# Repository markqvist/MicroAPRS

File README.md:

MicroAPRS
==========

__Important!__ _For new projects, please consider using [OpenModem](https://github.com/markqvist/OpenModem) as a platform instead. It is much more powerful, and has none of the limitations of this implementation. For simple projects, MicroAPRS is absolutely still usable, and it is incredibly stable and well-tested in thousands of hours of real-life usage, but have a look at OpenModem as well, since that is what I will be maintaining from now on. No new features or updates will be added to MicroAPRS from here on. I consider it stable and feature-complete for what the hardware is capable of._

MicroAPRS is an APRS firmware for [MicroModem](http://unsigned.io/micromodem). It supports both normal KISS mode, and a simple serial protocol for easy communication with an Arduino, or other MCU.

You can buy a complete modem from [my shop](http://unsigned.io/shop), or you can build one yourself pretty easily. Take a look at the documentation in the [MicroModem](https://github.com/markqvist/MicroModem) repository for information and getting started guides!

## Some features

- Send and receive AX.25 APRS packets
- Full modulation and demodulation in software
- Easy configuration of callsign and path settings
- Flexibility in how received packets are output over serial connection
- Persistent configuration stored in EEPROM
- Shorthand functions for sending location updates and messages, so you don't need to manually create the packets
- Ability to send raw packets
- Support for settings APRS symbols
- Support for power/height/gain info in location updates
- Ability to automatically ACK messages adressed to the modem
- Can run with open squelch
- Supports KISS mode for use with programs on a host computer

## KISS mode

When the modem is running in KISS mode, there's really not much more to it than connecting the modem to a computer, opening whatever program you want to use with it, and off you go.

When in KISS mode, the preamble time, tail time, persistence and slot time parameters can be configured by the default KISS commands for these. See KISS.h and KISS.c for more info on the configuration command syntax. 

It's important to note that some programs (Xastir, for example) will reset the modem when connecting to it, and then immediately send configuration commands. Depending on your hardware, this might have the unfortunate effect that the configuration commands are sent to the bootloader, instead of the booted firmware. If your program does not allow you to disable resetting or to set a delay for sending the configuration commands, you can manually disable the reset functionality by connecting a resistor of around 100 ohms between the VCC and DTR pins. This will ensure that the modem is not reset, even if the host program sends a reset command.

## Modem control - SimpleSerial

If you want to use the SimpleSerial protocol, here's how to control the APRS modem over a serial connection. The modem accepts a variety of commands for setting options and sending packets. Generally a command starts with one or more characters defining the command, and then whatever data is needed to set the options for that command. Here's a list of the currently available commands:

## Serial commands

Command | Description
--- | :---
__!\<data>__  | Send raw packet
__@\<cmt>__ | Send location update (cmt = optional comment)
__#\<msg>__ | Send APRS message
&nbsp; | &nbsp;
__c\<call>__ |  Set your callsign
__d\<call>__ |  Set destination callsign
__1\<call>__ |  Set PATH1 callsign
__2\<call>__ |  Set PATH2 callsign
&nbsp; | &nbsp;
__sc\<ssid>__ | Set your SSID
__sd\<ssid>__ | Set destination SSID
__s1\<ssid>__ | Set PATH1 SSID
__s2\<ssid>__ | Set PATH2 SSID
&nbsp; | &nbsp;
__lla\<LAT>__ | Set latitude (NMEA-format, eg 4903.50N)
__llo\<LON>__ | Set latitude (NMEA-format, eg 07201.75W)
__lp\<0-9>__  | Set TX power info
__lh\<0-9>__  | Set antenna height info
__lg\<0-9>__  | Set antenna gain info
__ld\<0-9>__  | Set antenna directivity info
__ls\<sym>__  | Select symbol
__lt\<s/a>__  | Select symbol table (standard/alternate)
&nbsp; | &nbsp;
__mc\<call>__ | Set message recipient callsign
__ms\<ssid>__ | Set message recipient SSID
__mr\<ssid>__ | Retry last message
__ma\<1/0>__  | Automatic message ACK on/off
&nbsp; |&nbsp;
__ps\<1/0>__  | Print SRC on/off
__pd\<1/0>__  | Print DST on/off
__pp\<1/0>__  | Print PATH on/off
__pm\<1/0>__  | Print DATA on/off
__pi\<1/0>__  | Print INFO on/off
__v\<1/0>__ | Verbose mode on/off
__V\<1/0>__ | Silent mode on/off
&nbsp; | &nbsp;
__w\<XXX>__ | Set preamble in ms
__W\<XXX>__ | Set TX tail in ms
&nbsp; | &nbsp;
__S__ | Save configuration
__L__ | Load configuration
__C__ | Clear configuration
__H__ | Print configuration

### Examples

__To set your callsign to XX1YYY-5, and then save the configuration, send these three commands:__
```
cXX1YYY
sc5
S
```

__To send an APRS message to ZZ5ABC-1 with the content "Hi there!", send these commands:__
```
mcZZ5ABC
ms1
# Hi there!
```

__To send a location update, with the comment "MicroAPRS", you can do something like this:__
```
lla5230.70N
llo01043.70E
@MicroAPRS
```

__To send an APRS message to ZZ5ABC-1 with the content "Hi there!", using a raw packet, send this command:__
```
!:ZZ5ABC-1 :Hi there!{01
```
__Here's an example of how to send a location update with power, height and gain information, using a raw packet:__
```
!=5230.70N/01043.70E-PHG2410MicroAPRS
```

### EEPROM Settings
When saving the configuration, it is written to EEPROM, so it will persist between poweroffs. If a configuration has been stored, it will automatically be loaded when the modem powers up. The configuration can be cleared by sending the "clear configuration" command (`C`).

### Serial Connection

To connect to the modem use __9600 baud, 8N1__ serial. By default, the firmware uses time-sensitive input, which means that it will buffer serial data as it comes in, and when it has received no data for a few milliseconds, it will start interpreting whatever it has received. This means you need to set your serial terminal program to not send data for every keystroke, but only on new-line, or pressing send or whatever. If you do not want this behaviour, you can compile the firmware with the DEBUG flag set, which will make the modem wait for a new-line character before interpreting the received data. I would generally advise against this though, since it means that you cannot have newline characters in whatever data you want to send!

The project has been implemented in your normal C with makefile style, and uses AVR Libc. The firmware is compatible with Arduino-based products, although it was not written in the Arduino IDE.

Visit [my site](http://unsigned.io) for questions, comments and other details.

## Support Me
If you have benefited from this project, you can help support the continued development of open, free and private communications systems by donating via one of the following channels:

- Ethereum: 0x81F7B979fEa6134bA9FD5c701b3501A2e61E897a
- Bitcoin: 3CPmacGm34qYvR6XWLVEJmi2aNe3PZqUuq
- Ko-Fi: https://ko-fi.com/markqvist

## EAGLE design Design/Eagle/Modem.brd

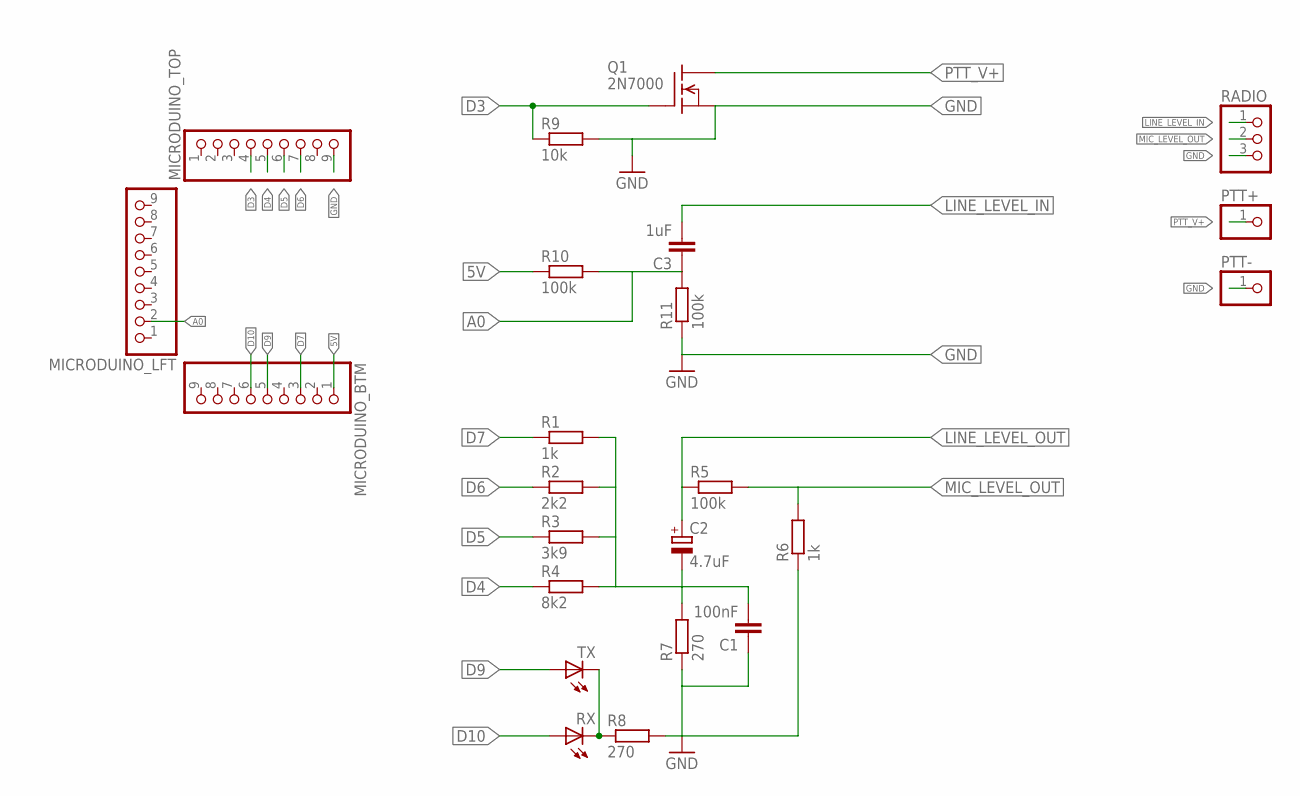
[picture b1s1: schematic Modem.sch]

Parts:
C1: 100nF; C2.5-2
C2: 4.7uF; E2,5-4R
C3: 1uF; C2.5-2
MICRODUINO_BTM: PINHD-1X9; 1X09-BIG
MICRODUINO_LFT: PINHD-1X9; 1X09-BIG
MICRODUINO_TOP: PINHD-1X9; 1X09-BIG
PTT+: PINHD-1X1; 1X01
PTT-: PINHD-1X1; 1X01
Q1: 2N7000; TO92
R1, R6: 1k; 0204V
R2: 2k2; 0204V
R3: 3k9; 0204V
R4: 8k2; 0204V
R5, R10, R11: 100k; 0204V
R7, R8: 270; 0204V
R9: 10k; 0204V
RADIO: PINHD-1X3; 1X03
RX: LED_ELD260; LED_LD260
TX: LED_ELD260; LED_LD260

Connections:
5V: MICRODUINO_BTM.1, R10.1
A0: C3.1, MICRODUINO_LFT.2, R10.2, R11.2
D3: MICRODUINO_TOP.4, Q1.1 (G), R9.1
D4: MICRODUINO_TOP.5, R4.1
D5: MICRODUINO_TOP.6, R3.1
D6: MICRODUINO_TOP.7, R2.1
D7: MICRODUINO_BTM.3, R1.1
D9: MICRODUINO_BTM.5, TX.A
D10: MICRODUINO_BTM.6, RX.A
GND: C1.1, MICRODUINO_TOP.9, PTT-.1, Q1.3 (S), R6.1, R7.1, R8.2, R9.2, R11.1, RADIO.3
LINE_LEVEL_IN: C3.2, RADIO.1
LINE_LEVEL_OUT: C2.+, R5.1
MIC_LEVEL_OUT: R5.2, R6.2, RADIO.2
unnamed: R8.1, RX.K (C), TX.K (C)
unnamed: C1.2, C2.-, R1.2, R2.2, R3.2, R4.2, R7.2
PTT_V+: PTT+.1, Q1.2 (D)

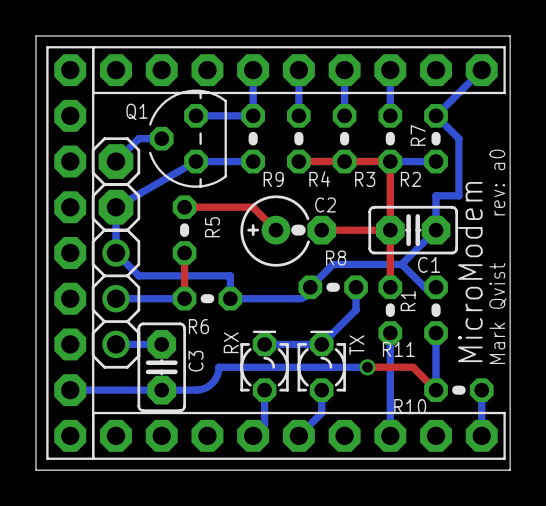
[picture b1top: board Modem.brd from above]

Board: 2 copper layers, 26.3 x 24.1 mm, 23 parts (0 on the bottom side), 16 nets.

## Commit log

2014-04-03 Working
2014-04-03 Buildrev
2014-04-03 Removed stuff
2014-04-03 Cleanup
2014-04-03 Still working
2014-04-03 Before afsk refactor
2014-04-03 Reworked AFSK Struct
2014-04-03 Reworked HDLC struct
2014-04-03 Reworked afsk init. Found the error :P
2014-04-03 Migrated adc_isr
2014-04-03 Migrated HDLC
2014-04-03 Migrated hardware
2014-04-03 Temporary AX.25 include for testing
2014-04-04 Reworked DAC ISR
2014-04-04 Reworked KFile read
2014-04-04 Reworked KFile write
2014-04-04 Reworked remaining KFile functions
2014-04-04 MP1 protocol receive implemented
2014-04-04 MP1 Transmit. Basic iplementation done.
2014-04-04 Implemented checksumming
2014-04-06 Commenting
2014-04-06 More commenting
2014-04-06 Cleaned up port mapping mess
2014-04-06 Removed dacPin sillyness
2014-04-06 Stuff not working
2014-04-07 Changed decode phase window
2014-04-07 Preamble timing
2014-04-07 Phase sync experiments
2014-04-08 Before PLL algo adjust
2014-04-09 Updated doc. Cleanup.
2014-04-10 Before AX.25 test
2014-04-10 After AX.25 decode test. 902 packets decoded.
2014-04-13 Before Hamming code
2014-04-13 Work on error correction
2014-04-13 Protocol-level (12,8) hamming code implemented
2014-04-13 Very short preamble
2014-04-14 After compression lib experiment
2014-04-14 Successfull compression test with heatshrink
2014-04-14 Compression tested over the air
2014-04-15 Before interleaver
2014-04-16 Interleaver implemented
2014-04-16 Updated documentation
2014-04-16 Fixed escape char bug
2014-04-17 12-byte interleaver
2014-04-17 12-byte interleaver, (12,8)-Hamming code and compression tested successfully
2014-04-23 8N1 Serial
2014-04-27 Direct serial line in/out. P-persistent CSMA. SLIP compatibility.
2014-04-27 Compression on/off compile option.
2014-04-28 Various TCP/IP experiments
2014-04-28 TCP mode
2014-04-29 Added schematics
2014-04-29 Update radme
2014-04-29 Updated Microduino PCB
2014-04-30 Update fritzing file
2014-04-30 Eagle files
2014-04-30 Added 3D sources for case
2014-04-30 Cast to signed int to squelch compiler warning
2014-04-30 Eagle PCB
2014-05-13 PCB confirmed
2014-05-13 Added photos
2014-05-13 Added photo
2014-05-16 Added binaries to repo
2014-05-17 Added license
2014-05-17 Added file
2014-05-17 Updated build instructions
2014-05-20 Added some documentation
2014-05-20 Updated quickstart
2014-05-20 Indentation mess cleanup
2014-05-29 32u4 experiment
2014-05-29 AX25 demo
2014-05-29 APRS demonstration
2014-06-18 Implemented simple serial control protocol for APRS stuff.
2014-06-18 Removed accidentially set frequency correction
2014-06-19 Implemented EEPROM settings
2014-06-19 Various simplifications and serial control improvements
2014-06-19 Implemented easy location update sending
2014-06-19 Implemented APRS messaging support
2014-06-19 Before auto-ack
2014-06-19 Implemented message auto-ack
2014-06-19 Update build
2014-06-23 Slimmed down binary
2014-06-23 Frame buf length define fixed
2014-06-24 Slimmed down BertOS AX25
2014-06-24 Fixed ack bug
2014-06-24 Fixed SSID config bug
2014-09-10 Adding an alternative hardware design-
2014-09-10 fixed readme
2014-11-09 Initial KISS support
2014-11-10 SimpleSerial configurable preamble and tail.
2014-11-19 Implemented P-persistent CSMA in KISS mode
2014-12-03 Before test
2014-12-04 KISS/AX.25 working
2014-12-18 Working build
2014-12-18 Serial stuff
2014-12-18 Various fixes
2014-12-19 Added readme and license
2014-12-19 Gitignore added
2014-12-19 Added precompiled binaries
2014-12-19 Deprecation notice
2014-12-19 BertOS wiped
2015-04-22 Just some housekeeping
2015-04-22 Fixed KISS bug where frame checksum would be sent to host
2015-04-22 Updated precompiled images
2015-04-24 Variable bitrate experiment
2015-04-26 Implemented selectable data rates
2015-04-26 Updated license notice
2015-07-22 Fix avr-size "Device: Unknown" message.
    Now avr-size show the target mcu and percent of space used.
2015-08-05 Increased max frame length. Other minor tweaks.
2015-08-22 Fixed SSID input validation
2015-08-23 Fixed error with message SSID not accepting single digit numbers.
2015-10-02 Refactoring to make explicit D-to-A and PTT pins & ports, and turning on and off PTT. This should also help to make porting to another chip easier.
2015-10-02 Fix some compile-time warnings.
2015-11-17 Rolling back changes from a7a167c19ba03fcdf118c07345fa3656f09369ea that broke the build. Please test on actual hardware before pull-requesting "improvements"...
2017-04-16 Fix broken Markdown headings
2018-03-28 Changed default preamble
2018-03-29 Gitignore
2018-04-24 Implemented KISS flow control
2018-04-24 Fixed stream setup io function declarations
2018-04-24 Improved data carrier detection
2018-11-28 Fixed a few typos
2018-12-01 Updated precompiled firmwares. Added TXWAIT option.
2020-01-26 Added schematic
